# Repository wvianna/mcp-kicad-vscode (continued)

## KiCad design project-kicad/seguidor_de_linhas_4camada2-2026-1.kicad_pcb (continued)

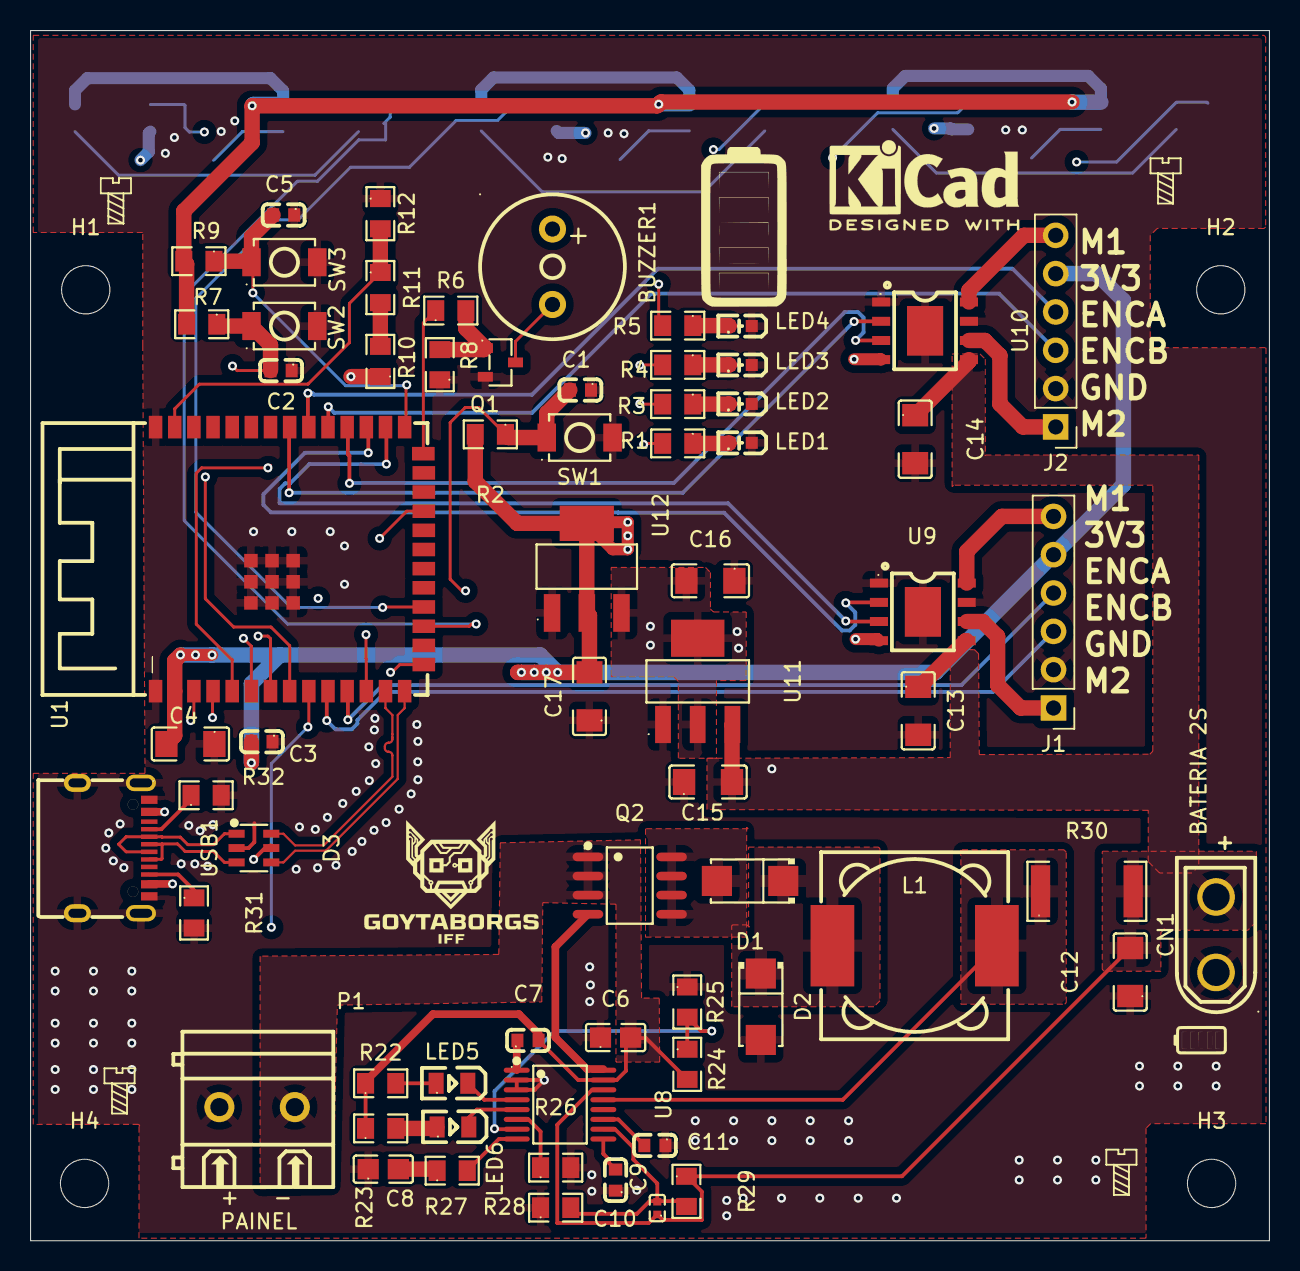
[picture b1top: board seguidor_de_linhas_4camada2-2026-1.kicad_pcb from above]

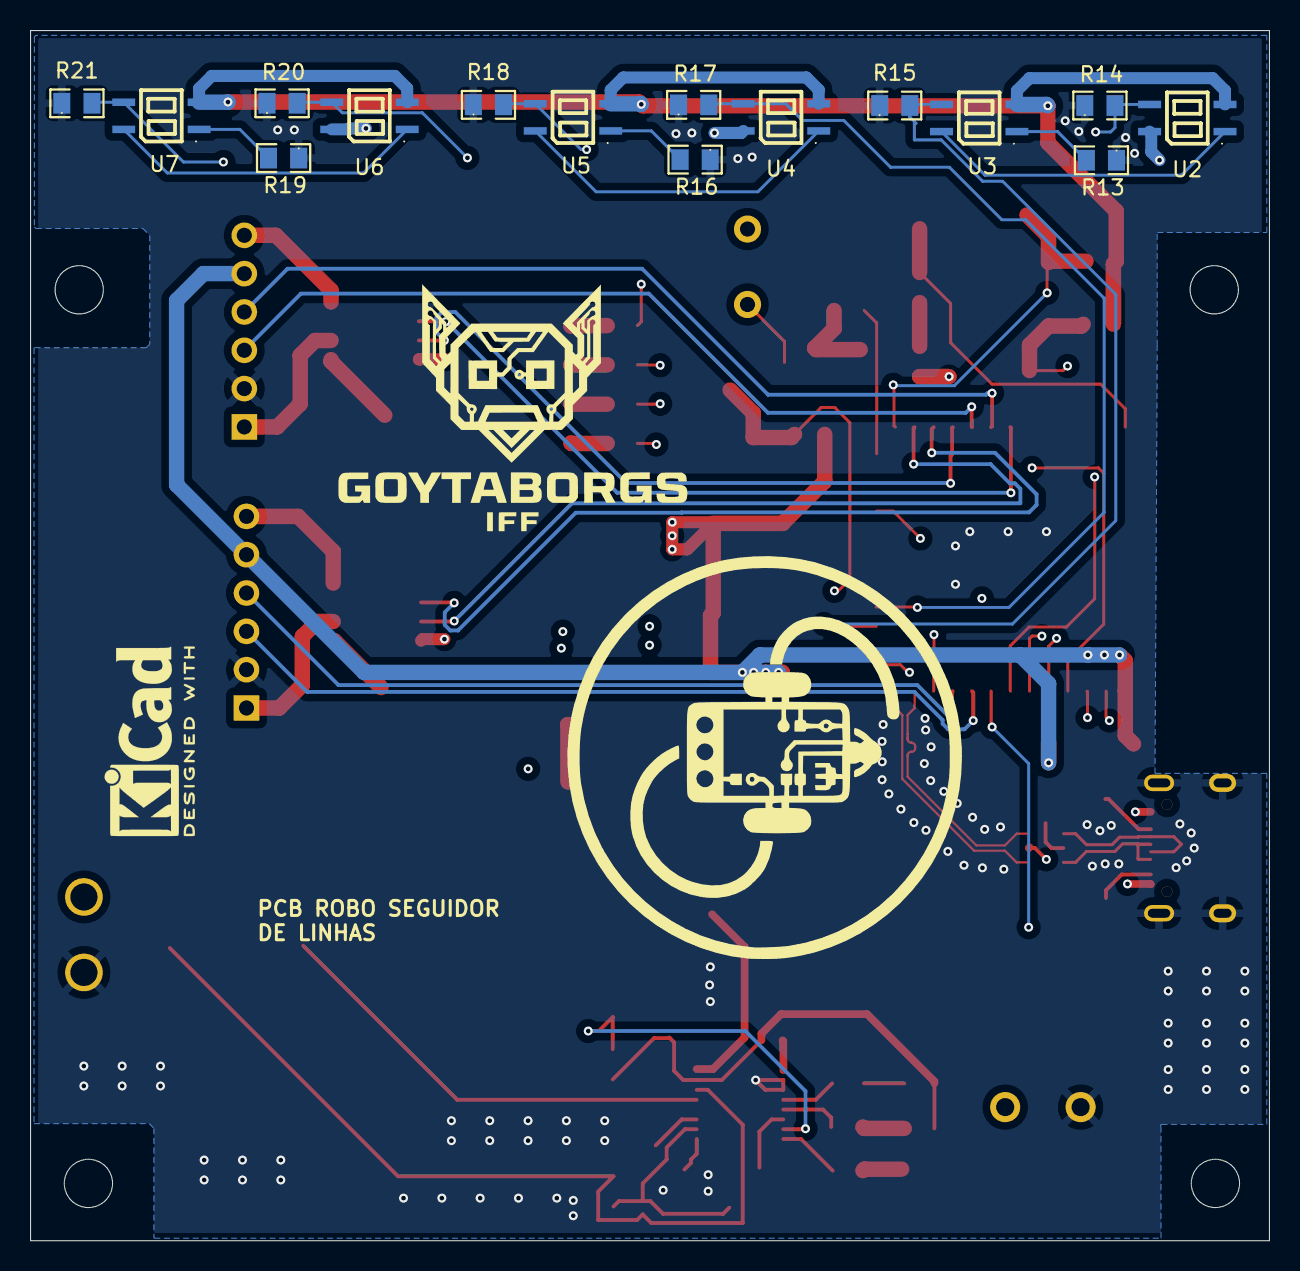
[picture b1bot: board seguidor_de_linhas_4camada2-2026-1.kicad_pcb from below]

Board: 4 copper layers, 82.1 x 80.2 mm, 86 parts (15 on the bottom side), 67 nets.
